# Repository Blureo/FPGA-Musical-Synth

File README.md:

FPGA-Musical-Synth
---
A musical synthesizer based on the iCE40 FPGA that outputs I2S audio.

Video demonstration of sine wave synth: https://youtu.be/_ejQGvuSiI

---

### 27 May 2026: Board bring-up is in progress!
The PCBs have been ordered and delivered! All that remains for that part is to bring the boards up and perform PCBA.

---

### 29 April 2026: Key Input PCB design complete!
The PCB for the input module has been completed. Each module represents 1 octave (12 keys). We decided to use shift registers to read key input in parallel and send out that data to the FPGA as serial (PISO). This provides a few advantages over other methods of key input:
1. **Fixed # of FPGA Pins**: We use a fixed number of pins on the FPGA for key input, regardless of how many keys we have.
2. **Daisy Chaining**: Shift registers can be daisy-chained to create a long line of parallel input with just one serial output. To take advantage of this, we designed the modules to daisy chain together, with each additional module in the line giving the user an additional octave.
3. **No Wasted PCBs**: PCB minimum order quantities (often 5) do not produce unused boards because these modules are made to be daisy-chained. If I have to order a minimum of 5 boards, and that's all I want to order, I get 5 octaves for my synth.

> The order for this PCB will be placed within a week or two; I am waiting to order it alongside PCBs for a class I'm currently taking. Because this PCB was designed to daisy-chain duplicates together, it was not designed with a place for an FPGA or the development board; that will be a separate module.

#### Current limitations:
1. FPGA still only supports one key press at a time.

---

### 12 March 2026: Numerically Controlled Oscillator (NCO)
Video demonstration of sine wave synth: https://youtu.be/_ejQGvuSiI8

The synth now makes sine waves by the Numerically-Controlled Oscillator (NCO)! This opens the door to make any kind of wave we want just by updating the ROMs. Additionally, a multi-clock cycle multiplication algorithm has been implemented to save space on the FPGA and take advantage of the 512 master clock cycles between one sample and the next.

#### Current limitations:
1. Only supports one key press at a time.

---

### 2 Feb 2026: Square Wave Synthesizer
Video demonstration of square wave synth: https://youtu.be/o0nXdgJRZlI

The wave_period_selector method of synthesis used is described by this process:
> wave_period_selector sends the half-period of the frequency (musical note) associated with the key pressed to i2s_transmitter. i2s_transmitter sends a square wave via I2S that oscillates every half-period (the one sent to it by wave_period_selector) to an I2S DAC. This generates a square wave at the desired frequency.

The square wave synth only supports one key press at a time. If multiple keys are pressed, the key that gets checked first in wave_period_selector is the note that gets played. Further, due to the nature of this synthesis, this only supports square waves.

---

### Hardware:
1. pico2-ice development board
2. Adafruit I2S 3W Class D Amplifier

### Software Tools:
##### 1. RTL Synthesis:
> OSS-CAD-SUITE is being used for iCE40 synthesis, Place-and-Route, as well as packing.
##### 2. Simulation:
> Icarus Verilog (iverilog) is being used for test bench simulation and other debugging. Verilator may replace icarus if it is decided that it is superior for testbenching this project's verilog modules.
##### 3. HDL:
> The FPGA was programmed in SystemVerilog.

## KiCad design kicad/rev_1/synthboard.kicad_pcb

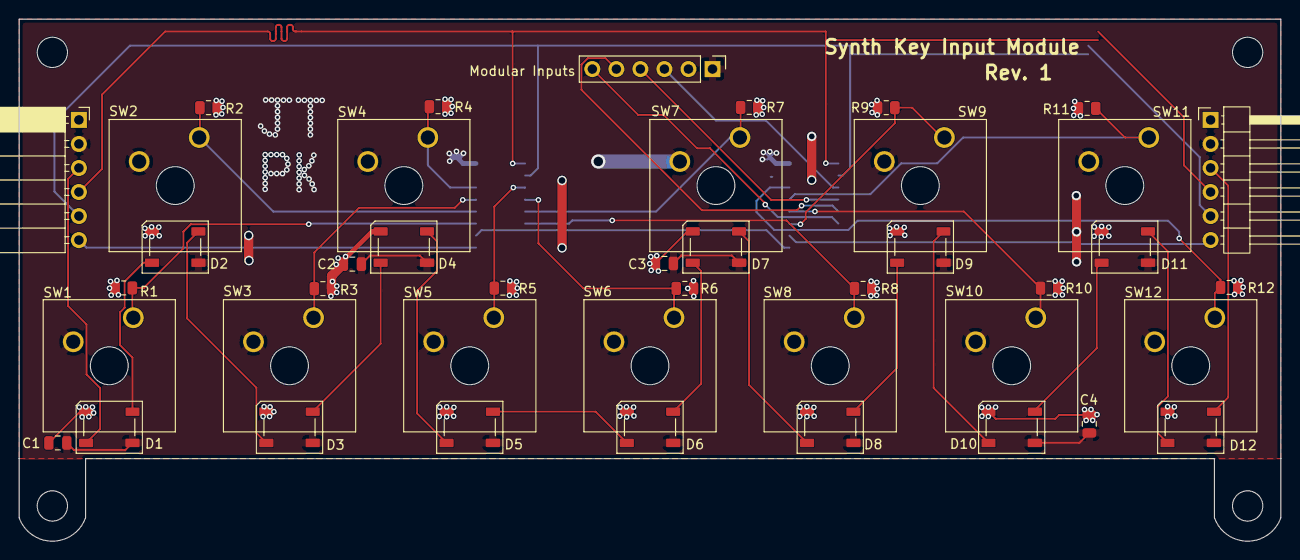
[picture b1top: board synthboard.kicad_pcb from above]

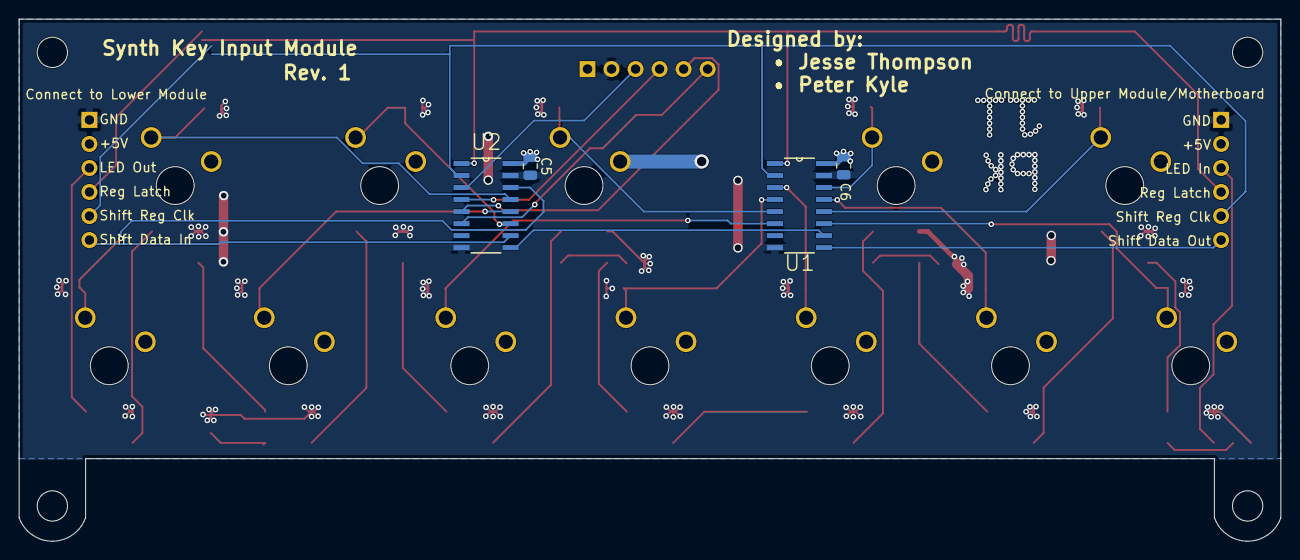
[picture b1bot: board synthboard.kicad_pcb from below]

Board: 2 copper layers, 133.3 x 55.2 mm, 51 parts (4 on the bottom side), 36 nets.

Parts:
C1, C2, C3, C4, C5, C6: 0.1 µF; C_0805_2012Metric
D1, D2, D3, D4, D5, D6, D7, D8, D9, D10, D11, D12: WS2812B; LED_WS2812B_PLCC4_5.0x5.0mm_P3.2mm
H1, H2, H3, H4: MountingHole; MountingHole_3.2mm_M3
J1: Connect to Upper Module/Motherboard; PinSocket_1x06_P2.54mm_Horizontal
J2: Connect to Lower Module; PinHeader_1x06_P2.54mm_Horizontal
J3: Modular Inputs; PinHeader_1x06_P2.54mm_Vertical
R1, R2, R3, R4, R5, R6, R7, R8, R9, R10, R11, R12: 11k; R_0805_2012Metric
SW1, SW2, SW3, SW4, SW5, SW6, SW7, SW8, SW9, SW10, SW11, SW12: SW_Push; SW_Cherry_MX_1.00u_Plate
U1, U2: 74HC165; SOIC127P600X175-16N

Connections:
+5V: C1.1, C2.1, C3.1, C4.1, C5.1, C6.1, D1.1 (VDD), D2.1 (VDD), D3.1 (VDD), D4.1 (VDD), D5.1 (VDD), D6.1 (VDD), D7.1 (VDD), D8.1 (VDD), D9.1 (VDD), D10.1 (VDD), D11.1 (VDD), D12.1 (VDD), J1.2, J2.2, J3.1, SW1.2, SW2.2, SW3.2, SW4.2, SW5.2, SW6.2, SW7.2, SW8.2, SW9.2, SW10.2, SW11.2, SW12.2, U1.16 (VCC), U2.16 (VCC)
GND: C1.2, C2.2, C3.2, C4.2, C5.2, C6.2, D1.3 (VSS), D2.3 (VSS), D3.3 (VSS), D4.3 (VSS), D5.3 (VSS), D6.3 (VSS), D7.3 (VSS), D8.3 (VSS), D9.3 (VSS), D10.3 (VSS), D11.3 (VSS), D12.3 (VSS), J1.1, J2.1, J3.2, R1.1, R2.1, R3.1, R4.1, R5.1, R6.1, R7.1, R8.1, R9.1, R10.1, R11.1, R12.1, U1.8 (GND), U1.15 (~CE), U2.8 (GND), U2.15 (~CE)
LED Data In: D1.4 (DIN), J1.3
LED Data Out: D12.2 (DOUT), J2.3
Modular Input 1: J3.6, U2.6 (D7)
Modular Input 2: J3.5, U2.5 (D6)
Modular Input 3: J3.4, U2.4 (D5)
Modular Input 4: J3.3, U2.3 (D4)
unnamed: D1.2 (DOUT), D2.4 (DIN)
unnamed: D2.2 (DOUT), D3.4 (DIN)
unnamed: D3.2 (DOUT), D4.4 (DIN)
unnamed: D4.2 (DOUT), D5.4 (DIN)
unnamed: D5.2 (DOUT), D6.4 (DIN)
unnamed: D6.2 (DOUT), D7.4 (DIN)
unnamed: D7.2 (DOUT), D8.4 (DIN)
unnamed: D8.2 (DOUT), D9.4 (DIN)
unnamed: D9.2 (DOUT), D10.4 (DIN)
unnamed: D10.2 (DOUT), D11.4 (DIN)
unnamed: D11.2 (DOUT), D12.4 (DIN)
unnamed: U1.10 (DS), U2.9 (Q7)
SW1: R1.2, SW1.1, U1.11 (D0)
SW2: R2.2, SW2.1, U1.12 (D1)
SW3: R3.2, SW3.1, U1.13 (D2)
SW4: R4.2, SW4.1, U1.14 (D3)
SW5: R5.2, SW5.1, U1.3 (D4)
SW6: R6.2, SW6.1, U1.4 (D5)
SW7: R7.2, SW7.1, U1.5 (D6)
SW8: R8.2, SW8.1, U1.6 (D7)
SW9: R9.2, SW9.1, U2.11 (D0)
SW10: R10.2, SW10.1, U2.12 (D1)
SW11: R11.2, SW11.1, U2.13 (D2)
SW12: R12.2, SW12.1, U2.14 (D3)
Shift Data In: J2.6, U2.10 (DS)
Shift Data Out: J1.6, U1.9 (Q7)
Shift Reg Clock: J1.5, J2.5, U1.2 (CP), U2.2 (CP)
Shift Reg Latch: J1.4, J2.4, U1.1 (~PL), U2.1 (~PL)

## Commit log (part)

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2026-01-29 Enhance README with project details
    Added project status, hardware, and software tools sections to README.
2026-01-29 Correct Iverilog reference to Icarus Verilog in README
2026-01-30 synth module functional with half_period_selector
    tb_synth.sv appears to work. Now to try on hardware.
2026-01-31 wave_period_selector method of synthesis is functional in hardware
    The project is now functional in hardware! The primary error that has prevented past iterations from working was that the reset signal was not tied to the debounce modules in the top module. The test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
2026-02-03 changes to kiCAD files
    I've begun work on the PCB. I should note that this won't be complete until I transistion to using a Numerically-Controlled Oscillator (NCO) with greater precision than the current method.
2026-02-03 Rename project from FPGA-Synth to FPGA-Synthesizer
2026-02-04 Rename project from FPGA-Synthesizer to FPGA-Musical-Synth
2026-02-14 Developed NCO Theory and Test
    Uploaded whiteboard image of the first idea for implementation of the NCO logic in the fpga, as well as a python example showing some of the theory discussed.
2026-02-20 rearranging files + added modified i2s transmitter to NCO
2026-02-26 Update nco.sv
    Added waveform and waveform slope rom definitions.
2026-02-27 Updated README
    Updated status of the project
2026-03-01 Update nco.sv
    Added inputs and accumulator logic
2026-03-01 Update nco.sv
    Implemented nco_mute logic
2026-03-01 Update nco.sv
    Refined mute logic and added comment to explain how this module works.
2026-03-01 Update nco.sv
    Started to implement the linear interpolation logic, and added a comment explaining how we plan to prevent modifying register values in between partial serial transmissions causing problems.
2026-03-01 added modules and edited existing ones for NCO synth
    Added debouncer.sv, made tone_frequency_calculator to send increment values to NCO, adjusted i2s_transmitter
2026-03-01 Created clock divider module
    Created the clock divider module and began redoing the NCO module as it needs to be sequential but in an always_ff block, so a state machine is required.
2026-03-02 Implemented clock divider and populated waveform rom files
    I created a python script that supplies data used to populate rom .mem files. This data will later be put into the actual ROM units in the SV code.
2026-03-02 Update nco.sv
    Added code to populate the rom data, added some comments, and fixed a couple things.
2026-03-02 first draft of tb_i2s_transmitter
2026-03-02 First NCO Testbench Complete
    NCO is not working right, something is wrong with the slope waveform and the test bench can't currently handle negative values, but it does show promising results.
2026-03-02 Working NCO!
    The NCO testbench now works successfully! We get a very clean sine wave output!
2026-03-02 Updated top module for NCO synth
2026-03-02 Update synth.sv
    Instantiated the NCO module into the synth.sv
2026-03-02 updated top module
2026-03-02 Update nco.sv
    Fixed possible multiple edge sensitive events error.
2026-03-02 adjusted nco.sv
2026-03-02 first build
    unsure if it will work
2026-03-02 removed duplicate key1 input from tone_frequency_calculator
2026-03-02 Sine wave synthesis now works with the NCO
    Thank you Peter for helping make the NCO.
2026-03-02 Revise README for feature updates and additional content
    Updated README with additional details about the synthesizer's features and status. Also added a youtube link for demonstration of the synth producing sine waves with the NCO
2026-03-02 Add ADSR Envelope section to README
    Added section on ADSR Envelope to enhance synth sound dynamics.
2026-03-05 Working Booth's Algorithm!
2026-05-08 PCB vanity edit
    changed solder mask color to purple in PCB editor so that the 3D viewer shows a purple board.
    I did not change the image in the README because the angle of the board makes the purple looks quite dark, so for the sake of an image, the green works better.
2026-05-12 made README formatting clearer
    Updated README with additional project milestones and video links.
2026-05-18 renamed a project folder
    renamed the folder containing the key input module KiCad project to more accurately reflect what it contains, as there might be a totally different PCB in the future that has all the computation on i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
2026-05-27 Updated README and file structure
    Added recent news about PCBs to the README, cleaned up how the local project library is handled in KiCad, and changed sub-folder structure for the KiCad folder.
2026-06-06 FreeCAD keyswitch Plate Addition
    There is now a plate for precisely fitting keyswitches into their sockets. Design in FreeCAD.
